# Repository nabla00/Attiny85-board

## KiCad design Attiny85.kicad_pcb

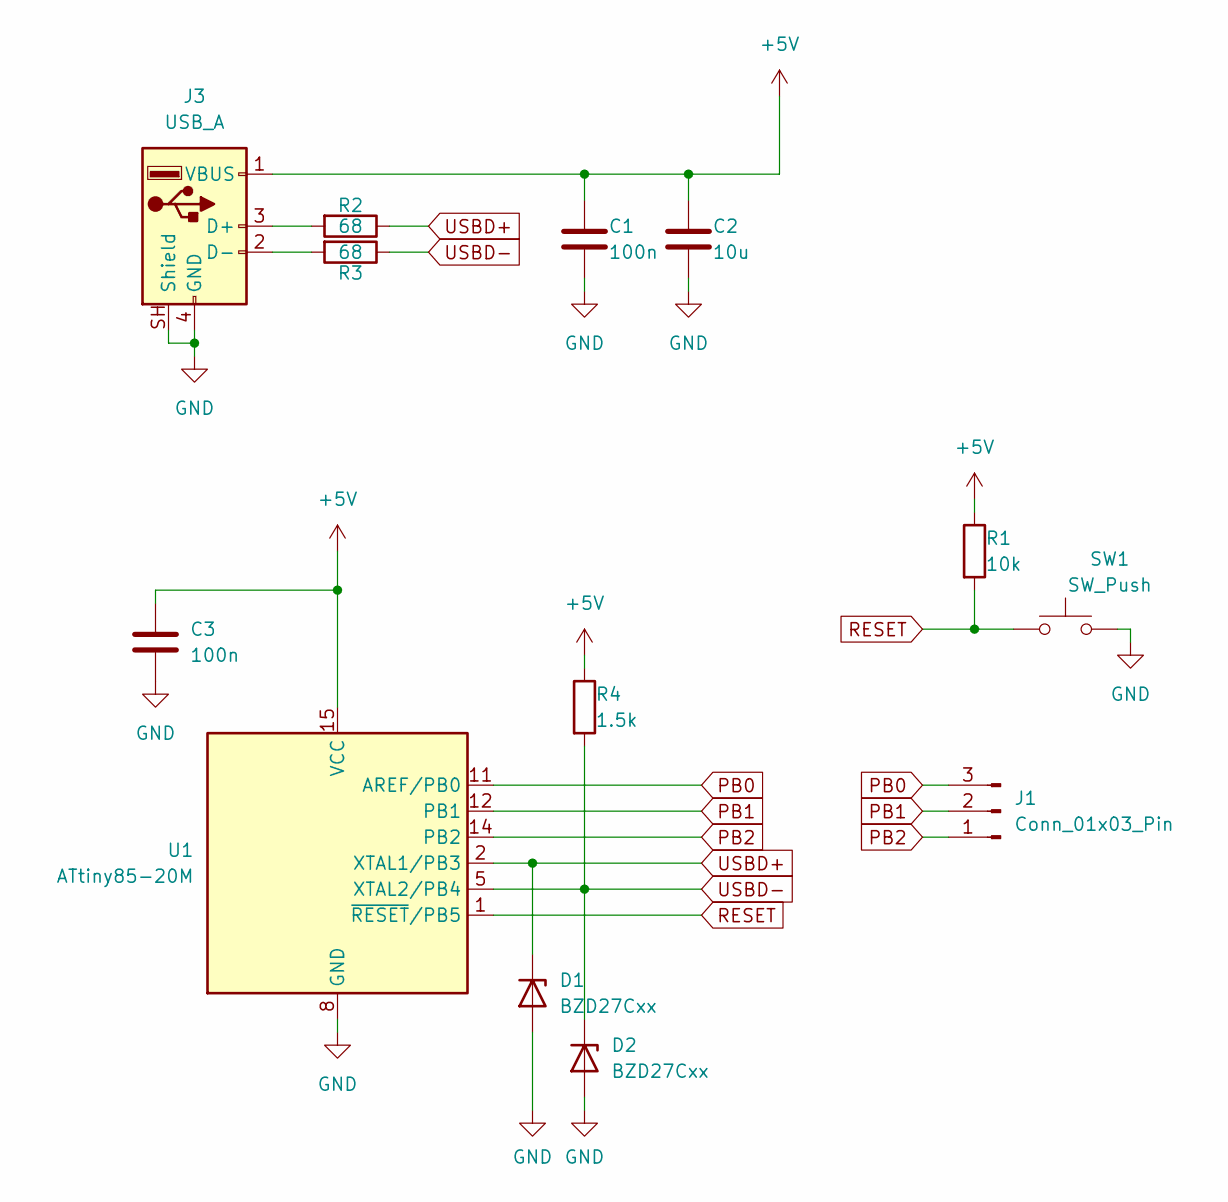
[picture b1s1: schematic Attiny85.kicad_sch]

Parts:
C1, C3: 100n; C_0805_2012Metric_Pad1.18x1.45mm_HandSolder
C2: 10u; C_0805_2012Metric_Pad1.18x1.45mm_HandSolder
D1, D2: BZD27Cxx; D_SMF
J1: Conn_01x03_Pin; PinHeader_1x03_P2.54mm_Vertical
J3: USB_A; USB_A_Receptacle_GCT_USB1046
R1: 10k; R_0805_2012Metric_Pad1.20x1.40mm_HandSolder
R2, R3: 68; R_0805_2012Metric_Pad1.20x1.40mm_HandSolder
R4: 1.5k; R_0805_2012Metric_Pad1.20x1.40mm_HandSolder
SW1: SW_Push; SW_Push_1P1T_NO_CK_KMR2
U1: ATtiny85-20M; QFN-20-1EP_4x4mm_P0.5mm_EP2.6x2.6mm

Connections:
+5V: C1.1, C2.1, C3.1, J3.1 (VBUS), R1.1, R4.1, U1.15 (VCC)
GND: C1.2, C2.2, C3.2, D1.2 (A), D2.2 (A), J3.4 (GND), J3.SH (Shield), SW1.2, U1.8 (GND), U1.21 (GND)
unnamed: J3.3 (D+), R2.2
unnamed: J3.2 (D-), R3.2
PB0: J1.3, U1.11 (AREF/PB0)
PB1: J1.2, U1.12 (PB1)
PB2: J1.1, U1.14 (PB2)
RESET: R1.2, SW1.1, U1.1 (~RESET/PB5)
USBD+: D1.1 (K), R2.1, U1.2 (XTAL1/PB3)
USBD-: D2.1 (K), R3.1, R4.2, U1.5 (XTAL2/PB4)

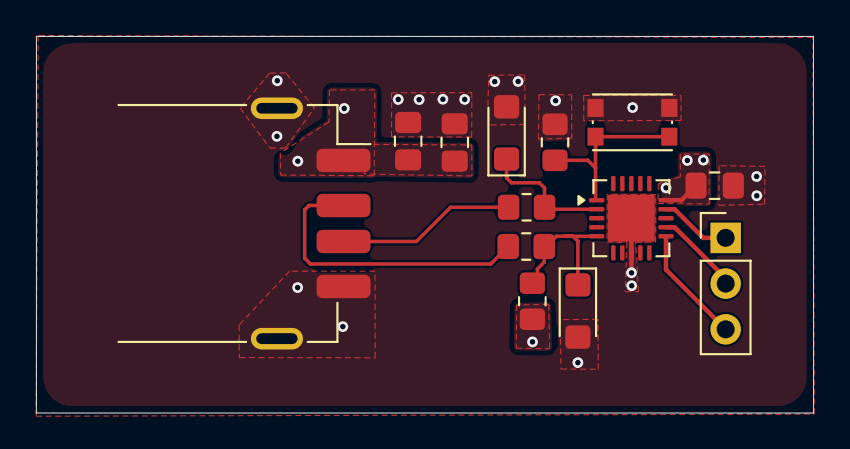
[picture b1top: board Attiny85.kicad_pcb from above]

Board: 4 copper layers, 43.2 x 20.9 mm, 13 parts (0 on the bottom side), 10 nets.
